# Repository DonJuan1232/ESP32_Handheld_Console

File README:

This project is for a self designed handheld console.
The idea is that I create a base framework so that other developers can easily create games for this "platform"

Because I wanted to learn how to design a PCB I decided to design a PCB (Also because I really didnt want to solder a lot of buttons to a prototype board :) )
Later in the projects life cycle I will add all the PCB and 3d model design files.

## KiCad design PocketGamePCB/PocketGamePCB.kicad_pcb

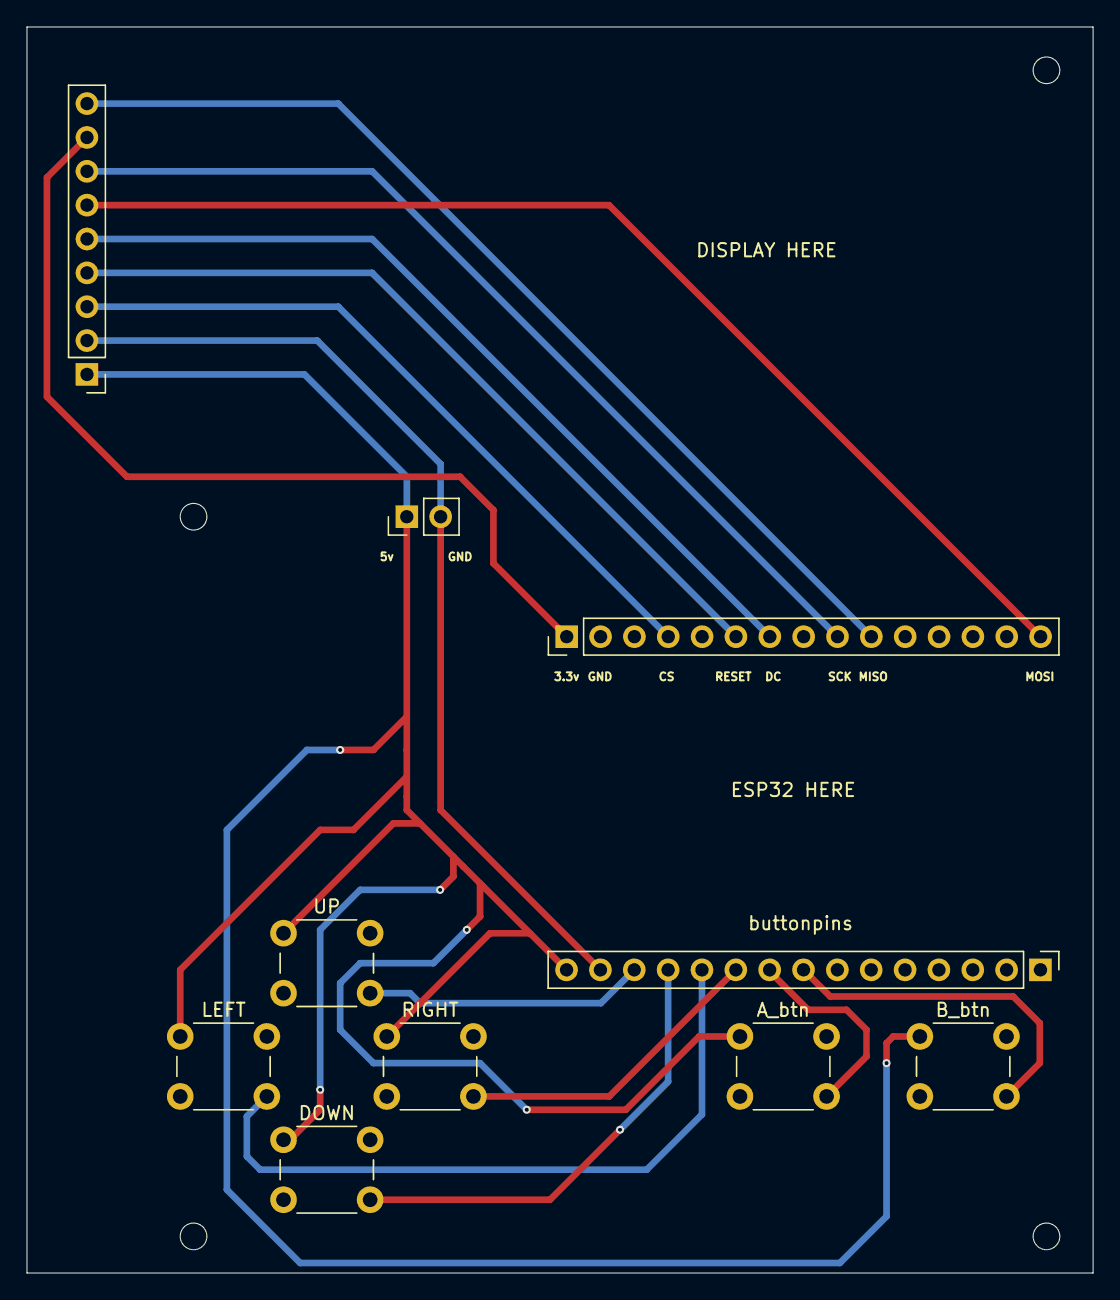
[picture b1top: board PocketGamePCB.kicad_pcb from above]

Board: 2 copper layers, 80.0 x 93.5 mm, 10 parts (0 on the bottom side), 15 nets.

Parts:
5v: Conn_01x02_Pin; PinHeader_1x02_P2.54mm_Vertical
A_btn: SW_Push; SW_PUSH_6mm_H5mm
B_btn: SW_Push; SW_PUSH_6mm_H5mm
DOWN: SW_Push; SW_PUSH_6mm_H5mm
J1: Conn_01x15_Pin; PinHeader_1x15_P2.54mm_Vertical
J2: Conn_01x09_Pin; PinHeader_1x09_P2.54mm_Vertical
LEFT: SW_Push; SW_PUSH_6mm_H5mm
RIGHT: SW_Push; SW_PUSH_6mm_H5mm
UP: SW_Push; SW_PUSH_6mm_H5mm
buttonpins: Conn_01x15_Pin; PinHeader_1x15_P2.54mm_Vertical

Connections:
unnamed: J1.1, J2.8
unnamed: J1.4, J2.3
unnamed: J1.6, J2.4
unnamed: J1.7, J2.5
unnamed: J1.9, J2.7
unnamed: J1.10, J2.9
unnamed: J1.15, J2.6
unnamed: 5v.1, J2.1, buttonpins.14
unnamed: 5v.2, A_btn.1, B_btn.1, DOWN.1, J2.2, LEFT.1, RIGHT.1, UP.1, buttonpins.15
unnamed: B_btn.2, buttonpins.8
unnamed: A_btn.2, buttonpins.9
unnamed: RIGHT.2, buttonpins.10
unnamed: LEFT.2, buttonpins.11
unnamed: DOWN.2, buttonpins.12
unnamed: UP.2, buttonpins.13

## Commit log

2025-08-26 Added project
    Added first prototype project code.
    PLAN:
    designed PCB for the project.
    Update code to more managable standard that can be easily modified for different types of games.
    add 3d models and PCB design to project files
2025-08-26 Add README with project overview and goals
    Added project description and goals for handheld console.
2025-09-29 added PCB files
2025-09-29 Added 3d models
2025-10-05 added files and BOM
